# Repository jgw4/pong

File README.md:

# About This Project

This repository contains an in-progress cleanroom reverse-engineering of the PCB for the original "PONG" arcade game released in 1972. A series of schematics is being created natively in KiCad based on a schematic created previously by "Dan" (see [PongSchematic.pdf](./doc/PongSchematic.pdf)), which itself was based off an original single-page released schematic from years ago. This schematic is then linked to a pcb file, which is ultimately intended to closely replicate the original Pong revision E circuit board, ideally as a 1:1 replacement.

The hope is that this can serve as:
1) a teaching tool for others who want to learn TTL logic
2) a diagnostic tool for those with existing pong boards
3) hobbyists that maybe want to create or modify the original board for themselves
4) a source for history and/or preservationist-minded people to appreciate the pong board digitally within a modern EDA, as PONG is considered a historically significant video game, and an impressive example of analog computing. With PONG games becoming rarer, older, and more in disrepair with each passing year, knowledge and information about the boards tend to become lost.

There are a few very useful documentation pieces out there, such as a 106-page dissection of the game by Dr. H. Holder, which I have mirrored within /doc/ in this repository.

# Status

This project is in very early stages. I have been working on this board on and off as other projects in my life come and go. If you have interest in this project, such as contributing information about the board, furthering the project, or whatever else, feel free to submit a PR or reach out.

## Schematic

The schematic is not yet complete, although all used chip symbols are placed on the root sheet

## PCB

TTL chips are roughly aligned in their final grid, although all other elements of the board are yet to be drawn or determined

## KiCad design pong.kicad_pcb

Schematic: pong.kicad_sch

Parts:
U1: L7805
UA2: 74LS107; pong_DIP-14_W7.62mm_Socket_LongPads
UA4: 7486; pong_DIP-14_W7.62mm_Socket_LongPads
UB5: 74LS74; pong_DIP-14_W7.62mm_Socket_LongPads
UC1: 7400; pong_DIP-14_W7.62mm_Socket_LongPads
UC2: 74LS74; pong_DIP-14_W7.62mm_Socket_LongPads
UC4: 7410; pong_DIP-14_W7.62mm_Socket_LongPads
UG6: 74LS107; pong_DIP-14_W7.62mm_Socket_LongPads

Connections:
+3.3V: UA4.14 (VCC), UC4.14 (VCC); also elsewhere on the board
GND: UA4.7 (GND), UC4.7 (GND); also elsewhere on the board

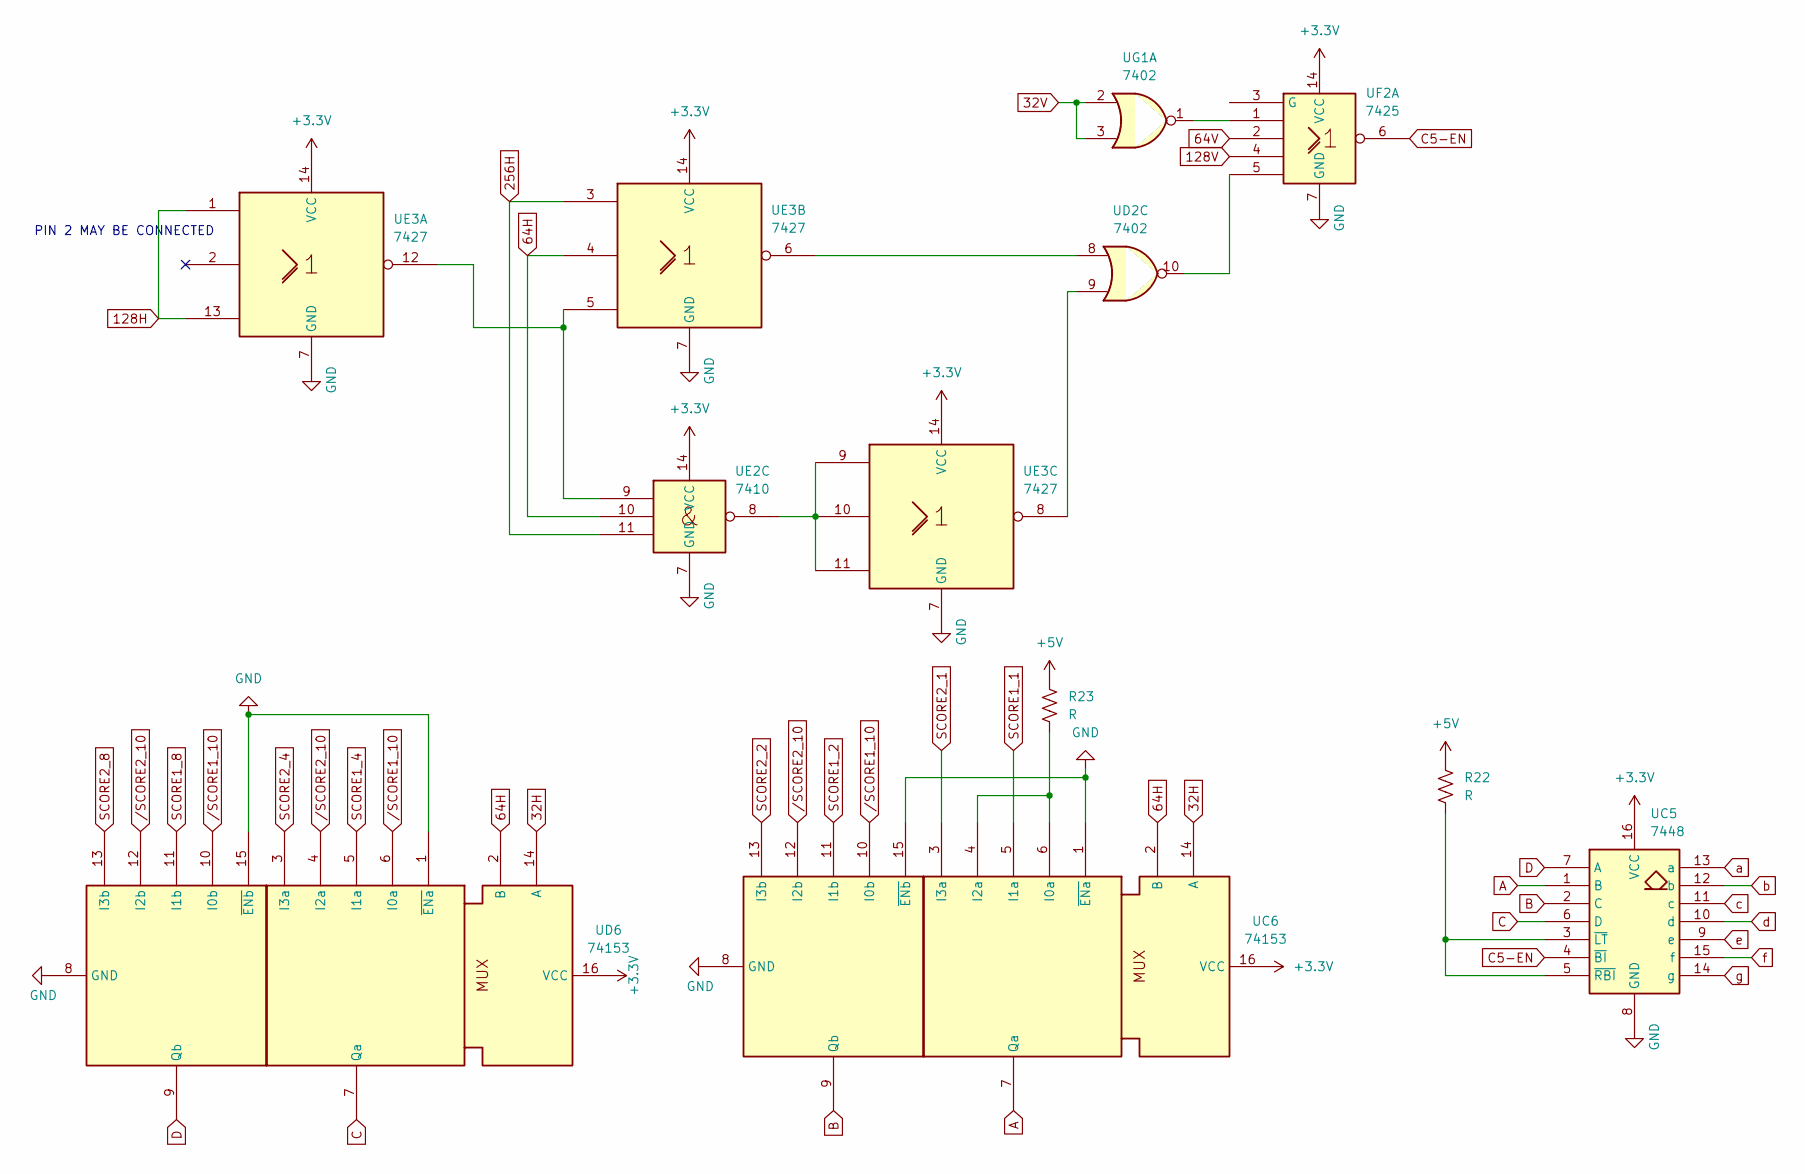
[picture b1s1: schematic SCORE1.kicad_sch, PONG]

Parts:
R22, R23: R; R_Axial_DIN0207_L6.3mm_D2.5mm_P10.16mm_Horizontal
UC5: 7448; pong_DIP-16_W7.62mm_Socket_LongPads
UC6: 74153; pong_DIP-16_W7.62mm_Socket_LongPads
UD2: 7402; pong_DIP-14_W7.62mm_Socket_LongPads
UD6: 74153; pong_DIP-16_W7.62mm_Socket_LongPads
UE2: 7410; pong_DIP-14_W7.62mm_Socket_LongPads
UE3: 7427; pong_DIP-14_W7.62mm_Socket_LongPads
UF2: 7425; pong_DIP-14_W7.62mm_Socket_LongPads
UG1: 7402; pong_DIP-14_W7.62mm_Socket_LongPads

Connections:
32H: UC6.14 (A), UD6.14 (A); also elsewhere on the board
32V: UG1.2, UG1.3; also elsewhere on the board
64H: UC6.2 (B), UD6.2 (B), UE2.10, UE3.4; also elsewhere on the board
64V: UF2.2
128H: UE3.1, UE3.13; also elsewhere on the board
128V: UF2.4
256H: UE2.11, UE3.3; also elsewhere on the board
+3.3V: R22.1, R23.1, UC5.16 (VCC), UC6.16 (VCC), UD6.16 (VCC), UE2.14 (VCC), UE3.14 (VCC), UF2.14 (VCC); also elsewhere on the board
A: UC5.1 (B), UC6.7 (Qa)
B: UC5.2 (C), UC6.9 (Qb)
C: UC5.6 (D), UD6.7 (Qa)
C5-EN: UC5.4 (~BI), UF2.6
D: UC5.7 (A), UD6.9 (Qb)
GND: UC5.8 (GND), UC6.1 (~ENa), UC6.8 (GND), UC6.15 (~ENb), UD6.1 (~ENa), UD6.8 (GND), UD6.15 (~ENb), UE2.7 (GND), UE3.7 (GND), UF2.7 (GND); also elsewhere on the board
unnamed: R22.2, UC5.3 (~LT), UC5.5 (~RBI)
unnamed: R23.2, UC6.4 (I2a), UC6.6 (I0a)
unnamed: UD2.8, UE3.6
unnamed: UD2.9, UE3.8
unnamed: UD2.10, UF2.5
unnamed: UE2.8, UE3.9, UE3.10, UE3.11
unnamed: UE2.9, UE3.5, UE3.12
unnamed: UF2.1, UG1.1
SCORE1_1: UC6.5 (I1a); also elsewhere on the board
SCORE1_2: UC6.11 (I1b); also elsewhere on the board
SCORE1_4: UD6.5 (I1a); also elsewhere on the board
SCORE1_8: UD6.11 (I1b); also elsewhere on the board
SCORE2_1: UC6.3 (I3a); also elsewhere on the board
SCORE2_2: UC6.13 (I3b); also elsewhere on the board
SCORE2_4: UD6.3 (I3a); also elsewhere on the board
SCORE2_8: UD6.13 (I3b); also elsewhere on the board
a: UC5.13 (a); also elsewhere on the board
b: UC5.12 (b); also elsewhere on the board
c: UC5.11 (c); also elsewhere on the board
d: UC5.10 (d); also elsewhere on the board
e: UC5.9 (e); also elsewhere on the board
f: UC5.15 (f); also elsewhere on the board
g: UC5.14 (g); also elsewhere on the board
/SCORE1_10: UC6.10 (I0b), UD6.6 (I0a), UD6.10 (I0b); also elsewhere on the board

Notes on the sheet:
PIN 2 MAY BE CONNECTED

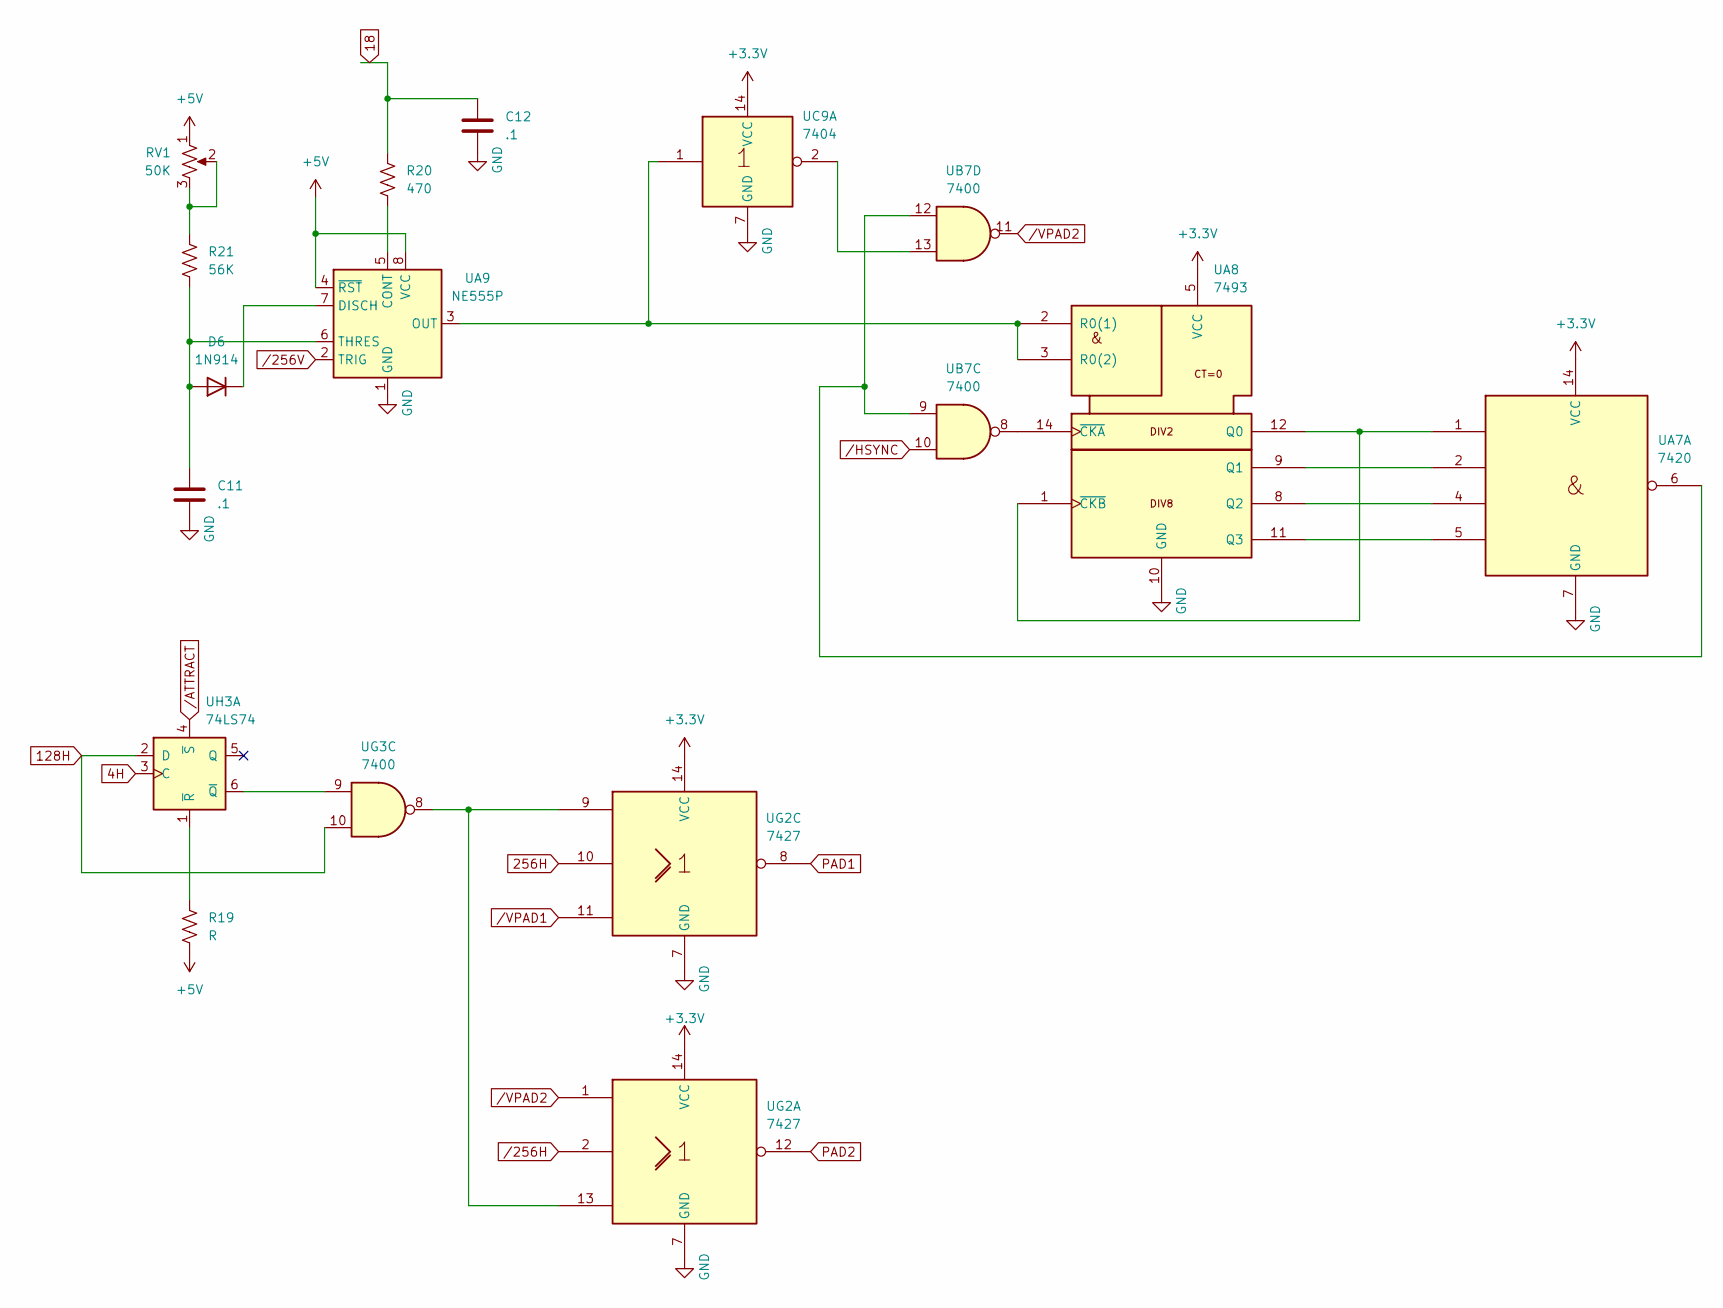
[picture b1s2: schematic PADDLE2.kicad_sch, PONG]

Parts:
C11, C12: .1; C_Axial_L3.8mm_D2.6mm_P10.00mm_Horizontal
D6: 1N914; D_DO-35_SOD27_P10.16mm_Horizontal
R19: R; R_Axial_DIN0207_L6.3mm_D2.5mm_P10.16mm_Horizontal
R20: 470; R_Axial_DIN0207_L6.3mm_D2.5mm_P10.16mm_Horizontal
R21: 56K; R_Axial_DIN0207_L6.3mm_D2.5mm_P10.16mm_Horizontal
RV1: 50K; Potentiometer_Bourns_3296Y_Vertical
UA7: 7420; pong_DIP-14_W7.62mm_Socket_LongPads
UA8: 7493; pong_DIP-14_W7.62mm_Socket_LongPads
UA9: NE555P; DIP-8_W7.62mm_Socket_LongPads
UB7: 7400; pong_DIP-14_W7.62mm_Socket_LongPads
UC9: 7404; pong_DIP-14_W7.62mm_Socket_LongPads
UG2: 7427; pong_DIP-14_W7.62mm_Socket_LongPads
UG3: 7400; pong_DIP-14_W7.62mm_Socket_LongPads
UH3: 74LS74; pong_DIP-14_W7.62mm_Socket_LongPads

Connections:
4H: UH3.3 (C); also elsewhere on the board
128H: UG3.10, UH3.2 (D); also elsewhere on the board
256H: UG2.10; also elsewhere on the board
+3.3V: R19.2, RV1.1, UA7.14 (VCC), UA8.5 (VCC), UA9.4 (~RST), UA9.8 (VCC), UC9.14 (VCC), UG2.14 (VCC); also elsewhere on the board
GND: C11.2, C12.2, UA7.7 (GND), UA8.10 (GND), UA9.1 (GND), UC9.7 (GND), UG2.7 (GND); also elsewhere on the board
unnamed: C12.1, R20.1
unnamed: C11.1, D6.2 (A), R21.2, UA9.6 (THRES)
unnamed: D6.1 (K), UA9.7 (DISCH)
unnamed: R21.1, RV1.2, RV1.3
unnamed: UA7.6, UB7.9, UB7.12
unnamed: UA7.1, UA8.1 (~CKB), UA8.12 (Q0)
unnamed: UA7.2, UA8.9 (Q1)
unnamed: UA7.4, UA8.8 (Q2)
unnamed: UA7.5, UA8.11 (Q3)
unnamed: UA8.2 (R0(1)), UA8.3 (R0(2)), UA9.3 (OUT), UC9.1
unnamed: UA8.14 (~CKA), UB7.8
unnamed: R20.2, UA9.5 (CONT)
unnamed: UB7.13, UC9.2
unnamed: UG2.9, UG2.13, UG3.8
unnamed: UG3.9, UH3.6 (~Q)
unnamed: R19.1, UH3.1 (~R)
PAD1: UG2.8; also elsewhere on the board
PAD2: UG2.12; also elsewhere on the board
/256H: UG2.2; also elsewhere on the board
/256V: UA9.2 (TRIG); also elsewhere on the board
/ATTRACT: UH3.4 (~S); also elsewhere on the board
/HSYNC: UB7.10; also elsewhere on the board
/VPAD1: UG2.11; also elsewhere on the board
/VPAD2: UB7.11, UG2.1

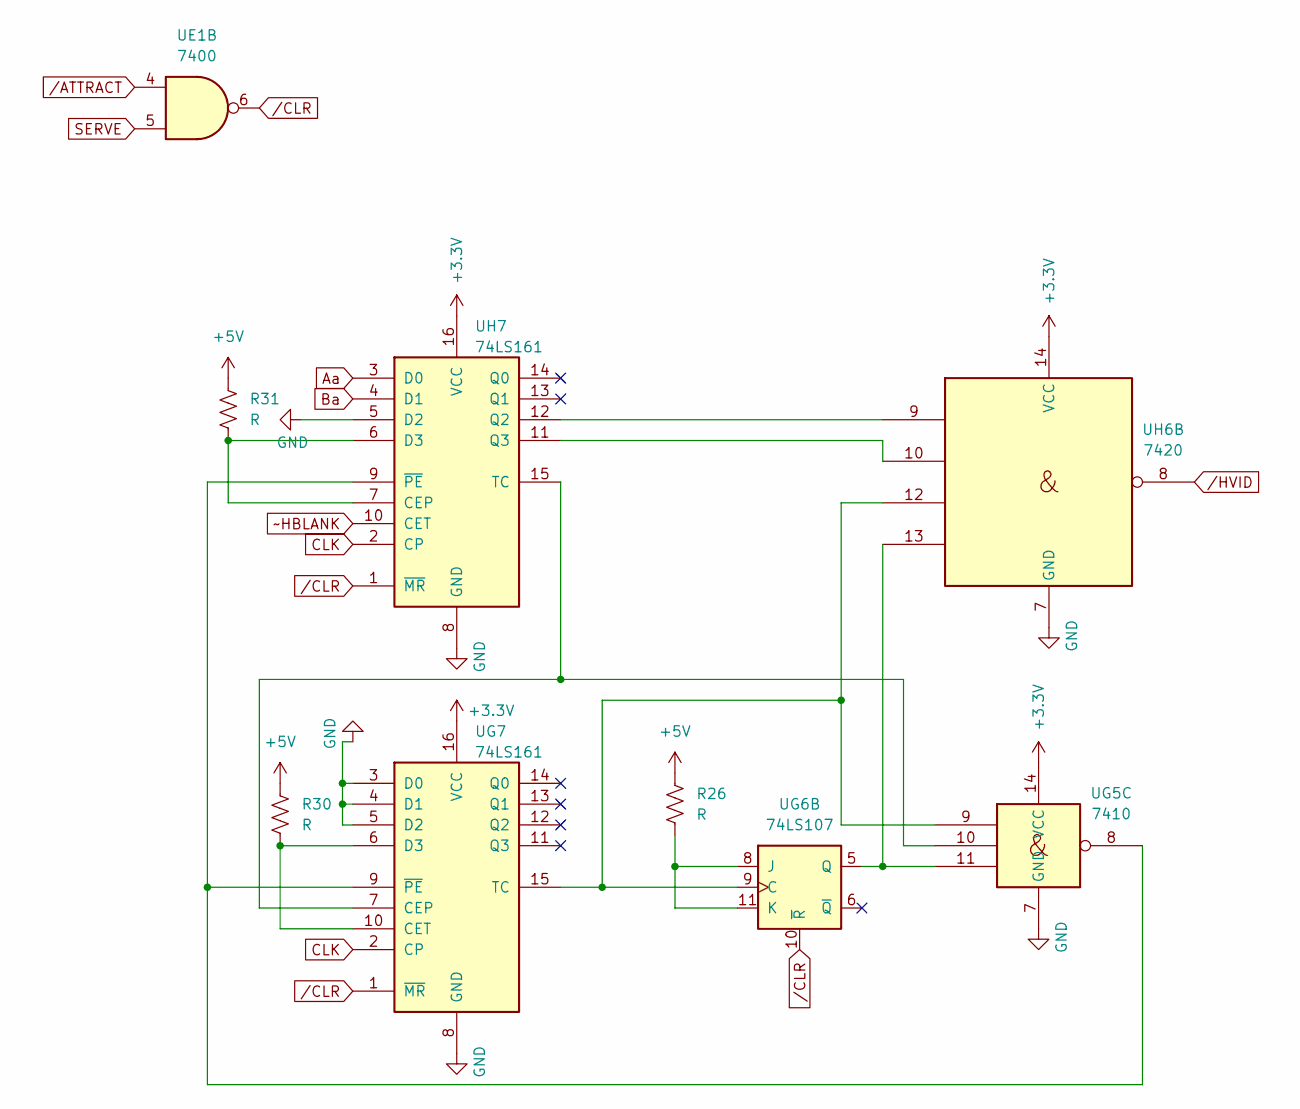
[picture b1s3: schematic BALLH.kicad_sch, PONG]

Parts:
R26, R30, R31: R; R_Axial_DIN0207_L6.3mm_D2.5mm_P10.16mm_Horizontal
UE1: 7400; pong_DIP-14_W7.62mm_Socket_LongPads
UG5: 7410; pong_DIP-14_W7.62mm_Socket_LongPads
UG6: 74LS107; pong_DIP-14_W7.62mm_Socket_LongPads
UG7: 74LS161; pong_DIP-16_W7.62mm_Socket_LongPads
UH6: 7420; pong_DIP-14_W7.62mm_Socket_LongPads
UH7: 74LS161; pong_DIP-16_W7.62mm_Socket_LongPads

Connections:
+3.3V: R26.1, R30.1, R31.1, UG5.14 (VCC), UG7.16 (VCC), UH6.14 (VCC), UH7.16 (VCC); also elsewhere on the board
Aa: UH7.3 (D0); also elsewhere on the board
Ba: UH7.4 (D1)
CLK: UG7.2 (CP), UH7.2 (CP); also elsewhere on the board
GND: UG5.7 (GND), UG7.3 (D0), UG7.4 (D1), UG7.5 (D2), UG7.8 (GND), UH6.7 (GND), UH7.5 (D2), UH7.8 (GND); also elsewhere on the board
unnamed: UG5.9, UG6.9 (C), UG7.15 (TC), UH6.12
unnamed: R26.2, UG6.8 (J), UG6.11 (K)
unnamed: UG5.11, UG6.5 (Q), UH6.13
unnamed: UG5.10, UG7.7 (CEP), UH7.15 (TC)
unnamed: R30.2, UG7.6 (D3), UG7.10 (CET)
unnamed: UG5.8, UG7.9 (~PE), UH7.9 (~PE)
unnamed: R31.2, UH7.6 (D3), UH7.7 (CEP)
unnamed: UH6.9, UH7.12 (Q2)
unnamed: UH6.10, UH7.11 (Q3)
SERVE: UE1.5
/ATTRACT: UE1.4; also elsewhere on the board
/CLR: UE1.6, UG6.10 (~R), UG7.1 (~MR), UH7.1 (~MR)
~HBLANK: UH7.10 (CET)

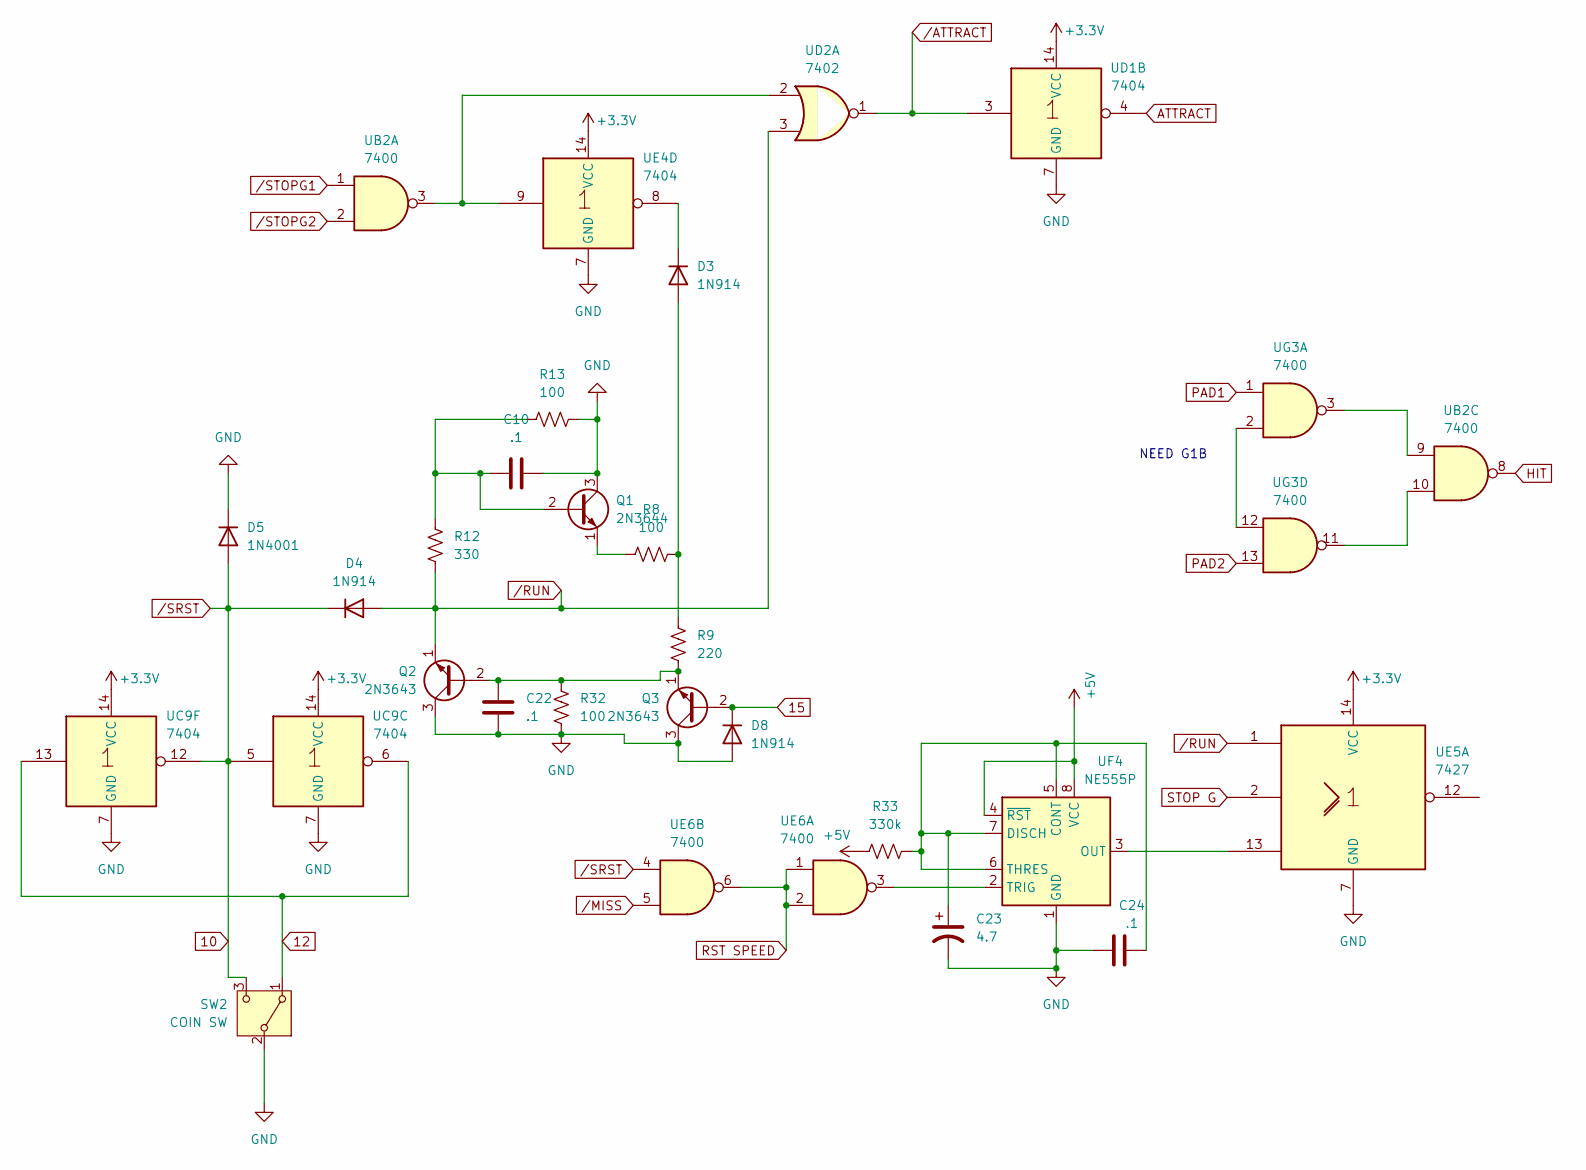
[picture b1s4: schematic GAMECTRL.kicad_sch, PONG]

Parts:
C10, C22, C24: .1; C_Axial_L3.8mm_D2.6mm_P10.00mm_Horizontal
C23: 4.7; C_Axial_L3.8mm_D2.6mm_P10.00mm_Horizontal
D3, D4, D8: 1N914; D_DO-35_SOD27_P10.16mm_Horizontal
D5: 1N4001; D_DO-41_SOD81_P10.16mm_Horizontal
Q1: 2N3644
Q2, Q3: 2N3643
R8, R13, R32: 100; R_Axial_DIN0207_L6.3mm_D2.5mm_P10.16mm_Horizontal
R9: 220; R_Axial_DIN0207_L6.3mm_D2.5mm_P10.16mm_Horizontal
R12: 330; R_Axial_DIN0207_L6.3mm_D2.5mm_P10.16mm_Horizontal
R33: 330k; R_Axial_DIN0207_L6.3mm_D2.5mm_P10.16mm_Horizontal
SW2: COIN SW
UB2: 7400; pong_DIP-14_W7.62mm_Socket_LongPads
UC9: 7404; pong_DIP-14_W7.62mm_Socket_LongPads
UD1: 7404; pong_DIP-14_W7.62mm_Socket_LongPads
UD2: 7402; pong_DIP-14_W7.62mm_Socket_LongPads
UE4: 7404; pong_DIP-14_W7.62mm_Socket_LongPads
UE5: 7427; pong_DIP-14_W7.62mm_Socket_LongPads
UE6: 7400; pong_DIP-14_W7.62mm_Socket_LongPads
UF4: NE555P; DIP-8_W7.62mm_Socket_LongPads
UG3: 7400; pong_DIP-14_W7.62mm_Socket_LongPads

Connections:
+3.3V: R33.2, UC9.14 (VCC), UD1.14 (VCC), UE4.14 (VCC), UE5.14 (VCC), UF4.4 (~RST), UF4.8 (VCC); also elsewhere on the board
ATTRACT: UD1.4; also elsewhere on the board
GND: C10.1, C22.2, C23.2, C24.2, D5.1 (K), D8.2 (A), Q1.3 (C), Q2.3 (C), Q3.3 (C), R13.1, R32.1, SW2.2 (B), UC9.7 (GND), UD1.7 (GND), UE4.7 (GND), UE5.7 (GND), UF4.1 (GND); also elsewhere on the board
HIT: UB2.8; also elsewhere on the board
unnamed: D3.2 (A), R8.2, R9.2
unnamed: D3.1 (K), UE4.8
unnamed: D8.1 (K), Q3.2 (B)
unnamed: C10.2, Q1.2 (B), R12.2, R13.2
unnamed: Q1.1 (E), R8.1
unnamed: C22.1, Q2.2 (B), Q3.1 (E), R9.1, R32.2
unnamed: UB2.3, UD2.2, UE4.9
unnamed: UB2.9, UG3.3
unnamed: UB2.10, UG3.11
unnamed: SW2.1 (A), UC9.6, UC9.13
unnamed: C23.1, C24.1, R33.1, UF4.5 (CONT), UF4.6 (THRES), UF4.7 (DISCH)
unnamed: UE5.13, UF4.3 (OUT)
unnamed: UE6.3, UF4.2 (TRIG)
unnamed: UG3.2, UG3.12
PAD1: UG3.1; also elsewhere on the board
PAD2: UG3.13; also elsewhere on the board
RST SPEED: UE6.1, UE6.2, UE6.6; also elsewhere on the board
STOP G: UE5.2
/ATTRACT: UD1.3, UD2.1; also elsewhere on the board
/MISS: UE6.5; also elsewhere on the board
/RUN: D4.2 (A), Q2.1 (E), R12.1, UD2.3, UE5.1
/SRST: D4.1 (K), D5.2 (A), SW2.3 (C), UC9.5, UC9.12, UE6.4; also elsewhere on the board
/STOPG1: UB2.1; also elsewhere on the board

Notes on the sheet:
NEED G1B

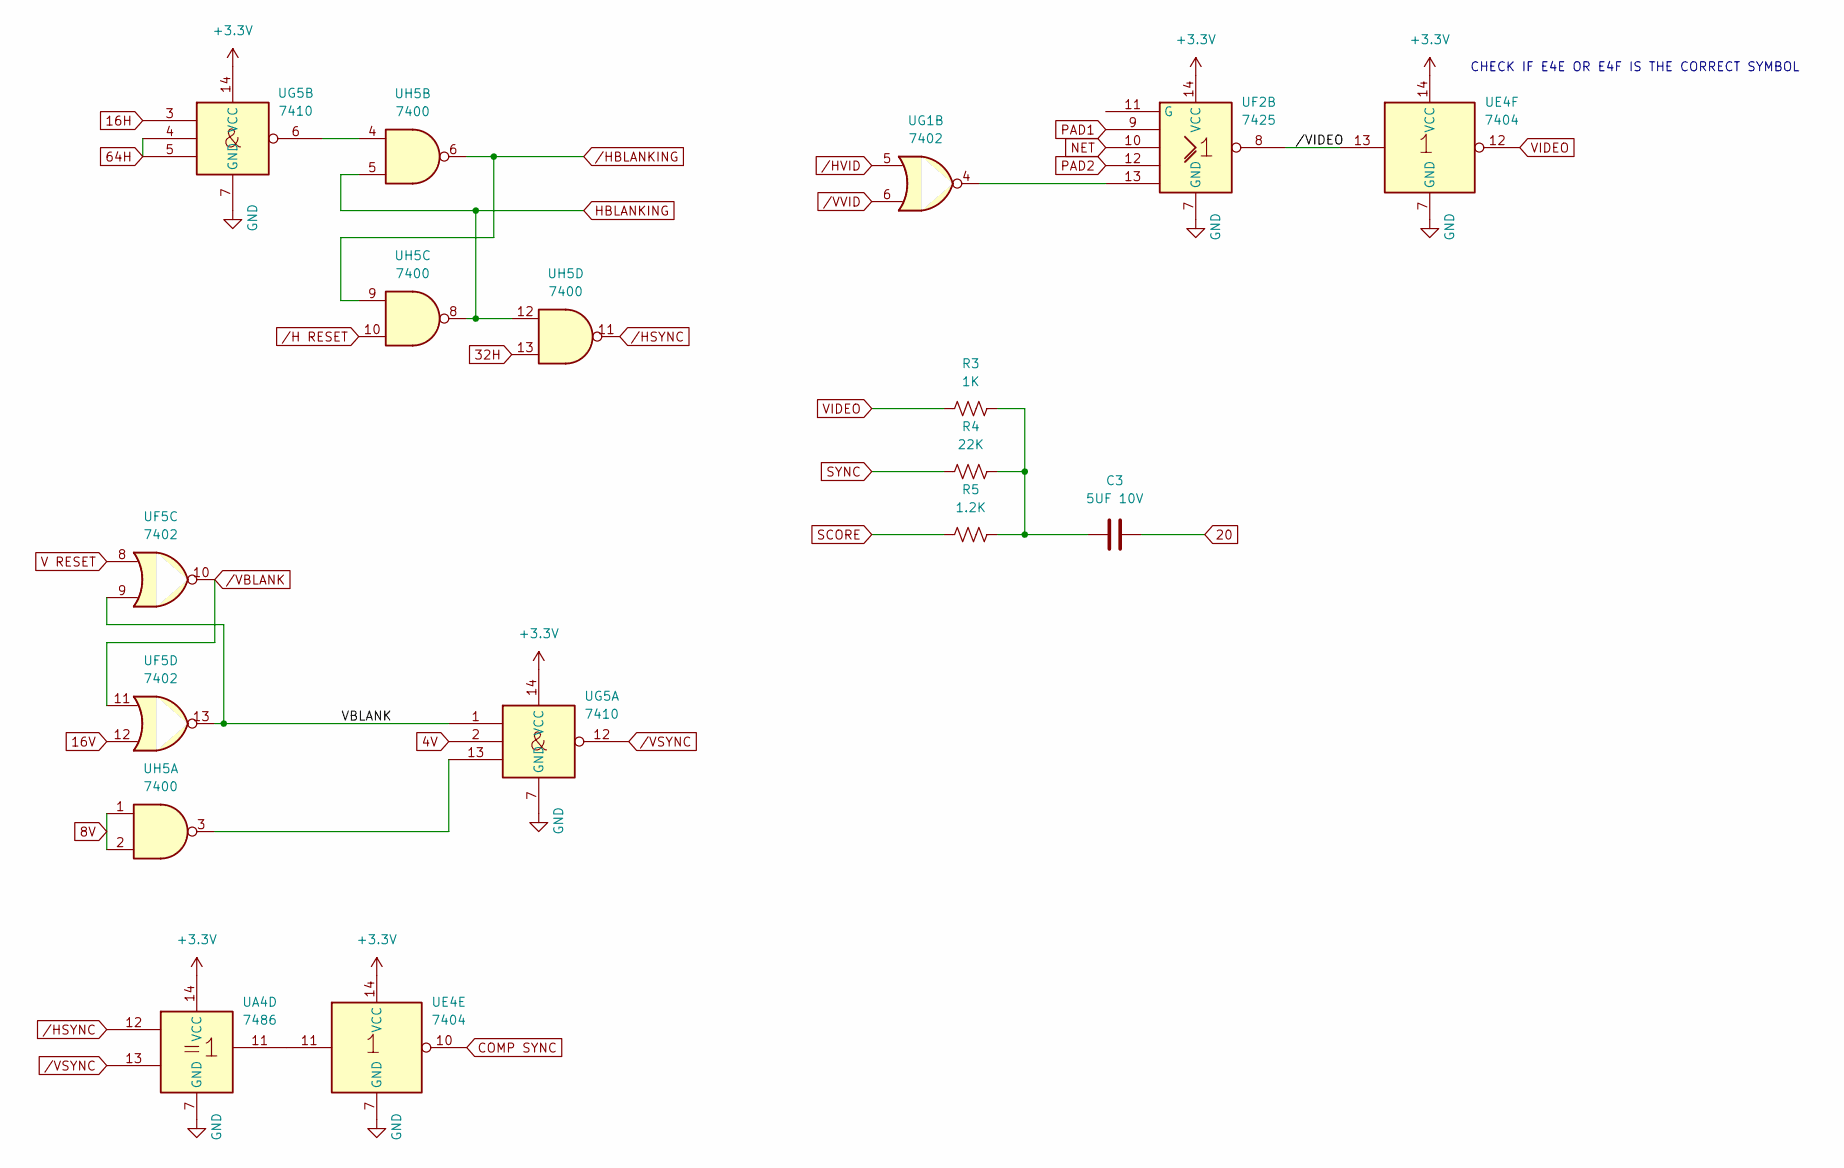
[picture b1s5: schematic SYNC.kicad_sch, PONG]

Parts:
C3: 5UF 10V
R3: 1K; R_Axial_DIN0207_L6.3mm_D2.5mm_P10.16mm_Horizontal
R4: 22K; R_Axial_DIN0207_L6.3mm_D2.5mm_P10.16mm_Horizontal
R5: 1.2K; R_Axial_DIN0207_L6.3mm_D2.5mm_P10.16mm_Horizontal
UA4: 7486; pong_DIP-14_W7.62mm_Socket_LongPads
UE4: 7404; pong_DIP-14_W7.62mm_Socket_LongPads
UF2: 7425; pong_DIP-14_W7.62mm_Socket_LongPads
UF5: 7402; pong_DIP-14_W7.62mm_Socket_LongPads
UG1: 7402; pong_DIP-14_W7.62mm_Socket_LongPads
UG5: 7410; pong_DIP-14_W7.62mm_Socket_LongPads
UH5: 7400; pong_DIP-14_W7.62mm_Socket_LongPads

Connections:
4V: UG5.2; also elsewhere on the board
8V: UH5.1, UH5.2; also elsewhere on the board
16H: UG5.3; also elsewhere on the board
16V: UF5.12; also elsewhere on the board
32H: UH5.13; also elsewhere on the board
64H: UG5.4, UG5.5; also elsewhere on the board
+3.3V: UA4.14 (VCC), UE4.14 (VCC), UF2.14 (VCC), UG5.14 (VCC); also elsewhere on the board
/SYNC/VBLANK: UF5.9, UF5.13, UG5.1
/SYNC//VIDEO: UE4.13, UF2.8
COMP SYNC: UE4.10
GND: UA4.7 (GND), UE4.7 (GND), UF2.7 (GND), UG5.7 (GND); also elsewhere on the board
HBLANKING: UH5.5, UH5.8, UH5.12
NET: UF2.10; also elsewhere on the board
unnamed: C3.1, R3.2, R4.2, R5.2
unnamed: UA4.11, UE4.11
unnamed: UF2.13, UG1.4
unnamed: UG5.6, UH5.4
unnamed: UG5.13, UH5.3
PAD1: UF2.9; also elsewhere on the board
PAD2: UF2.12; also elsewhere on the board
SCORE: R5.1; also elsewhere on the board
SYNC: R4.1
V RESET: UF5.8
VIDEO: R3.1, UE4.12
/H RESET: UH5.10
/HBLANKING: UH5.6, UH5.9
/HSYNC: UA4.12, UH5.11; also elsewhere on the board
/VBLANK: UF5.10, UF5.11; also elsewhere on the board
/VSYNC: UA4.13, UG5.12
/VVID: UG1.6; also elsewhere on the board

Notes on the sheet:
CHECK IF E4E OR E4F IS THE CORRECT SYMBOL

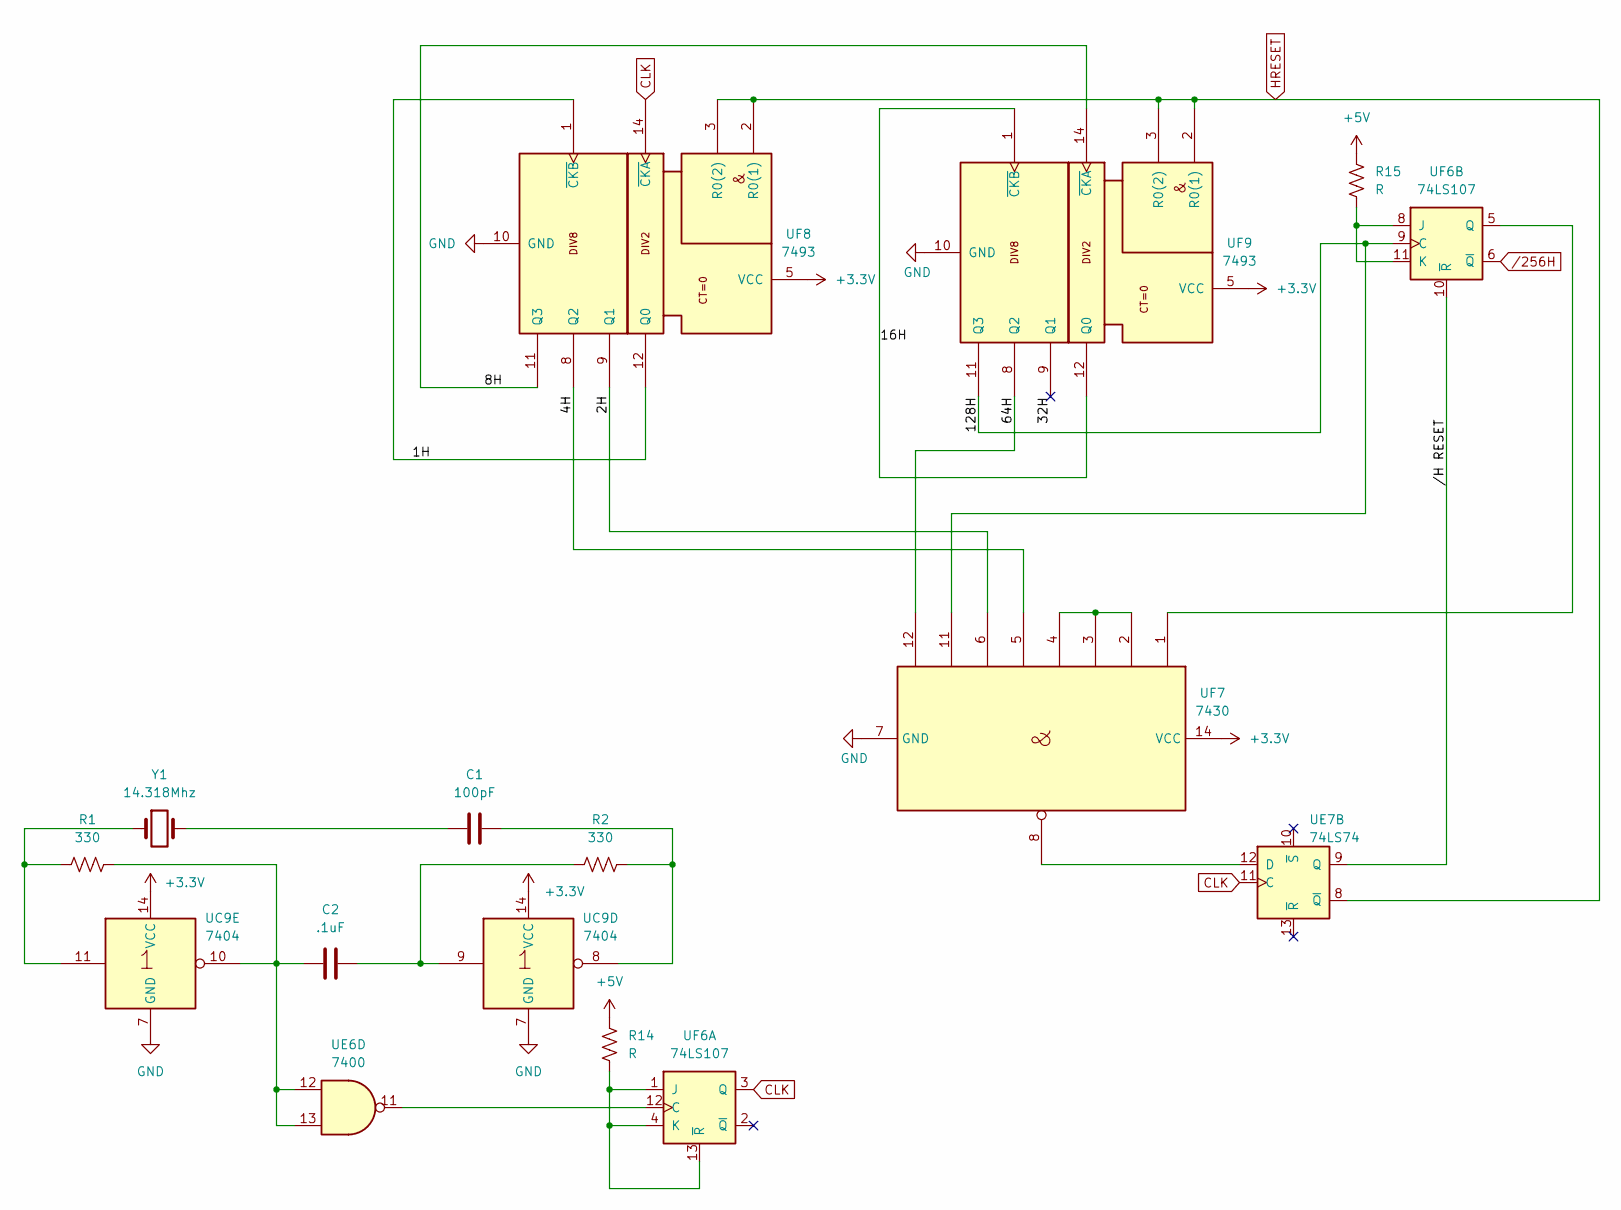
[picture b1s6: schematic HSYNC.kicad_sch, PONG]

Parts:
C1: 100pF; C_Disc_D10.5mm_W5.0mm_P7.50mm
C2: .1uF; C_Disc_D10.5mm_W5.0mm_P7.50mm
R1, R2: 330; R_Axial_DIN0207_L6.3mm_D2.5mm_P10.16mm_Horizontal
R14, R15: R; R_Axial_DIN0207_L6.3mm_D2.5mm_P10.16mm_Horizontal
UC9: 7404; pong_DIP-14_W7.62mm_Socket_LongPads
UE6: 7400; pong_DIP-14_W7.62mm_Socket_LongPads
UE7: 74LS74; pong_DIP-14_W7.62mm_Socket_LongPads
UF6: 74LS107; pong_DIP-14_W7.62mm_Socket_LongPads
UF7: 7430; pong_DIP-14_W7.62mm_Socket_LongPads
UF8, UF9: 7493; pong_DIP-14_W7.62mm_Socket_LongPads
Y1: 14.318Mhz; Crystal_HC49-U_Vertical

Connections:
+3.3V: R14.1, R15.1, UC9.14 (VCC), UF7.14 (VCC), UF8.5 (VCC), UF9.5 (VCC); also elsewhere on the board
/HSYNC/1H: UF8.1 (~CKB), UF8.12 (Q0)
/HSYNC/2H: UF7.6, UF8.9 (Q1)
/HSYNC/4H: UF7.5, UF8.8 (Q2)
/HSYNC/8H: UF8.11 (Q3), UF9.14 (~CKA)
/HSYNC/16H: UF9.1 (~CKB), UF9.12 (Q0)
/HSYNC/32H: UF9.9 (Q1)
/HSYNC/64H: UF7.12, UF9.8 (Q2)
/HSYNC/128H: UF6.9 (C), UF7.11, UF9.11 (Q3)
/HSYNC//H RESET: UE7.9 (Q), UF6.10 (~R)
CLK: UE7.11 (C), UF6.3 (Q), UF8.14 (~CKA); also elsewhere on the board
GND: UC9.7 (GND), UF7.7 (GND), UF8.10 (GND), UF9.10 (GND); also elsewhere on the board
HRESET: UE7.8 (~Q), UF8.2 (R0(1)), UF8.3 (R0(2)), UF9.2 (R0(1)), UF9.3 (R0(2)); also elsewhere on the board
unnamed: C1.1, R2.1, UC9.8
unnamed: C1.2, Y1.2
unnamed: C2.1, R2.2, UC9.9
unnamed: C2.2, R1.1, UC9.10, UE6.12, UE6.13
unnamed: R1.2, UC9.11, Y1.1
unnamed: UE7.12 (D), UF7.8
unnamed: UE6.11, UF6.12 (C)
unnamed: R14.2, UF6.1 (J), UF6.4 (K), UF6.13 (~R)
unnamed: R15.2, UF6.8 (J), UF6.11 (K)
unnamed: UF6.5 (Q), UF7.1
unnamed: UF7.2, UF7.3, UF7.4
/256H: UF6.6 (~Q); also elsewhere on the board

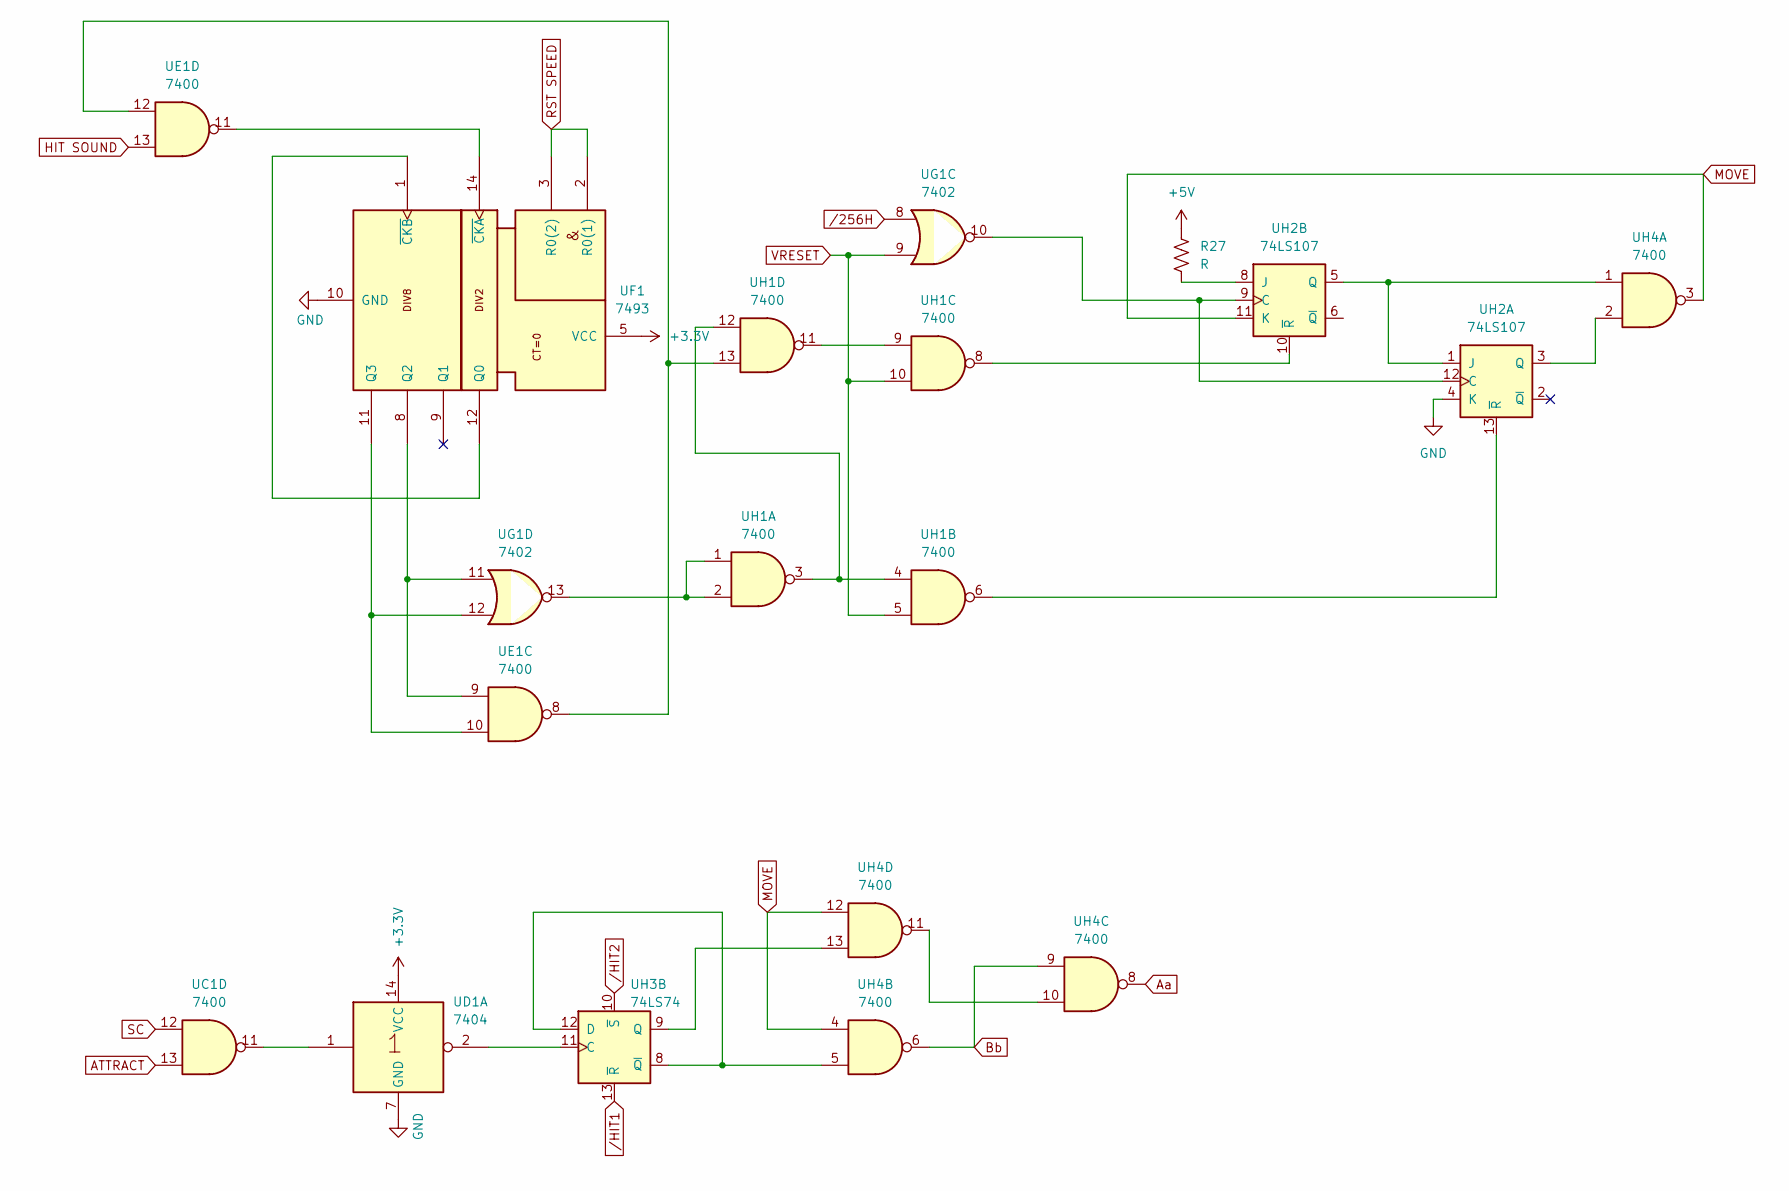
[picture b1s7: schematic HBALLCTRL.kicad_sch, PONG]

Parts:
R27: R; R_Axial_DIN0207_L6.3mm_D2.5mm_P10.16mm_Horizontal
UC1: 7400; pong_DIP-14_W7.62mm_Socket_LongPads
UD1: 7404; pong_DIP-14_W7.62mm_Socket_LongPads
UE1: 7400; pong_DIP-14_W7.62mm_Socket_LongPads
UF1: 7493; pong_DIP-14_W7.62mm_Socket_LongPads
UG1: 7402; pong_DIP-14_W7.62mm_Socket_LongPads
UH1, UH4: 7400; pong_DIP-14_W7.62mm_Socket_LongPads
UH2: 74LS107; pong_DIP-14_W7.62mm_Socket_LongPads
UH3: 74LS74; pong_DIP-14_W7.62mm_Socket_LongPads

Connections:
+3.3V: R27.1, UD1.14 (VCC), UF1.5 (VCC); also elsewhere on the board
ATTRACT: UC1.13; also elsewhere on the board
Aa: UH4.8; also elsewhere on the board
Bb: UH4.6, UH4.9
GND: UD1.7 (GND), UF1.10 (GND), UH2.4 (K); also elsewhere on the board
HIT SOUND: UE1.13
MOVE: UH2.11 (K), UH4.3, UH4.4, UH4.12
unnamed: UC1.11, UD1.1
unnamed: UE1.8, UE1.12, UH1.13
unnamed: UF1.1 (~CKB), UF1.12 (Q0)
unnamed: UE1.9, UF1.8 (Q2), UG1.11
unnamed: UE1.10, UF1.11 (Q3), UG1.12
unnamed: UE1.11, UF1.14 (~CKA)
unnamed: UG1.13, UH1.1, UH1.2
unnamed: UH1.9, UH1.11
unnamed: UH1.3, UH1.4, UH1.12
unnamed: UG1.10, UH2.9 (C), UH2.12 (C)
unnamed: UH2.1 (J), UH2.5 (Q), UH4.1
unnamed: UH2.3 (Q), UH4.2
unnamed: UH1.6, UH2.13 (~R)
unnamed: R27.2, UH2.8 (J)
unnamed: UH1.8, UH2.10 (~R)
unnamed: UD1.2, UH3.11 (C)
unnamed: UH3.8 (~Q), UH3.12 (D), UH4.5
unnamed: UH3.9 (Q), UH4.13
unnamed: UH4.10, UH4.11
RST SPEED: UF1.2 (R0(1)), UF1.3 (R0(2)); also elsewhere on the board
SC: UC1.12
VRESET: UG1.9, UH1.5, UH1.10
/256H: UG1.8; also elsewhere on the board
/HIT1: UH3.13 (~R)
/HIT2: UH3.10 (~S)
